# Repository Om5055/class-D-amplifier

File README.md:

# class-D-amplifier
it is class d amplifier that was created using totempole driver.

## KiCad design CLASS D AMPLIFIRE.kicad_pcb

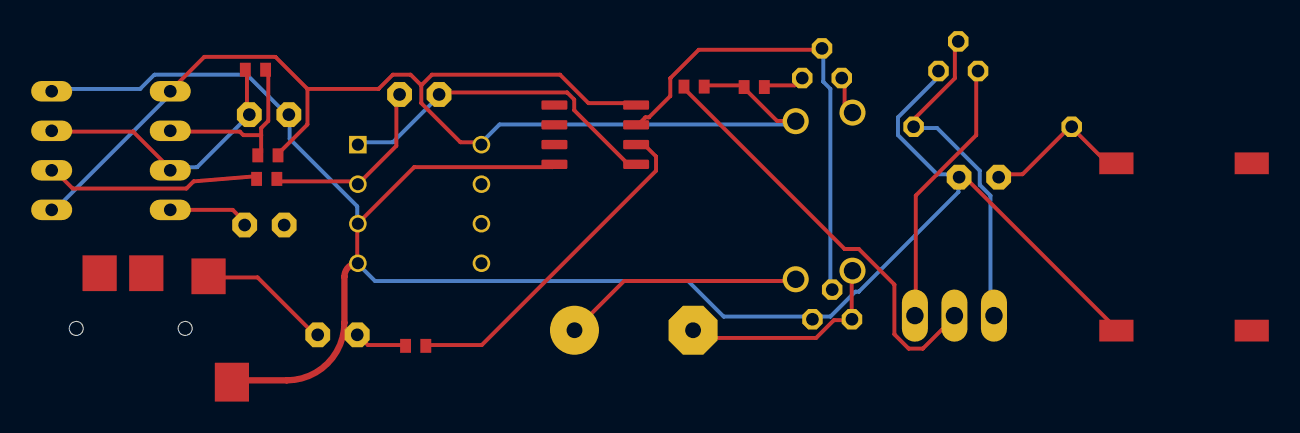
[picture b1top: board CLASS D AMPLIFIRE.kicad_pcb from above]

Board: 16 copper layers, 24 parts (0 on the bottom side), 20 nets.

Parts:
C1, C2, C3, C5, C6: C2.5-3
C4: E7,5-16
D1, D2: 1N4933; DO41-10
IC1: NE555; DIL-08
J1: SJ2-3574A-SMT-TR; SAMESKY_SJ2-3574A-SMT-TR
L1: 0207_10
Q1: 2N3906; TO92
Q2: BSS97; TO202
Q3: BSS92; TO92
R1, R2, R3, R9, R10, R11: R1005
SP1: SMS-1308MS-2-R
T1: 2N3904; TO92
U1: OPA2134PAG4; DIP794W45P254L959H508Q8
U2: LM393D; SOIC127P600X175-8N

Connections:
GND: C1.2, C2.2, IC1.1, J1.1, Q3.3, SP1.-, T1.3, U1.3, U1.4, U2.4
unnamed: Q2.3, Q3.1
unnamed: C4.-, D1.C, T1.1
unnamed: D1.A, Q1.1
unnamed: Q1.3, R2.1
unnamed: C5.2, U1.1, U2.5
unnamed: C4.+, D2.C
unnamed: Q1.2, T1.2, U2.7
unnamed: L1.1, Q2.1, Q3.2
unnamed: C1.1, L1.2, SP1.+
unnamed: C3.1, IC1.5
unnamed: Q2.2, R1.1
unnamed: IC1.7, R3.1, R9.2
unnamed: IC1.3, R11.1
unnamed: C2.1, IC1.2, IC1.6, R9.1
unnamed: C5.1, R11.2, U1.2
unnamed: C6.1, J1.2
unnamed: C6.2, R10.1
unnamed: R10.2, U2.6
VCC: D2.A, IC1.4, IC1.8, R1.2, R2.2, R3.2, U1.8, U2.8
